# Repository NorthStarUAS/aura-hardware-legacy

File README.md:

# AuraUAS Autopilot Hardware

This is a repository of hardware designs that have evolved out of the
AuraUAS project.  These designs serve the AuraUAS ecosystem.

## Version 1.0 - 1.4 (May 2015 - August 2016)

Beaglebone Black + Custom Cape + APM2

This is the first functional autopilot board design I created myself.
I have built up at least 4 flying autopilots from this design.
However, it leverages the old APM2 (atmega2560-based) board as the
sensor head.  This results actually are quite good, but it leads to a
stack of 3 boards and a fairly inefficient layout.  Also the APM2 is a
very old design now, has some limitations, and is only available through
clone outlets.

## Version 1.5 (January 2017)

Beaglebone Black + Custom Cape + Teensy-3.2

Although not listed as v1.5 in the file names, this is the logical
successor to the APM2-based board.  The APM2 is dropped and replaced
by a more modern teensy-3.2 paired with an IMU/Pressure breakout
board.  The teensy offers much more CPU power, more memory, better
ADC's, and native 3.3v ttl logic levels.

The system was breadboarded and the overall concept proved out.
However, before this design was finished or built, the pocketbeagle
became available.  This has prompted me to move to the next iteration.

## Version 2.0 - 2.1 (January 2018)

Pocketbeagle + Teensy-3.2 + Custom Board (designed with Express PCB)

This is a single board that combines a pocketbeagle + teensy + imu
breakout + voltage regulator + connectors in a single board package
that has only slightly larger footprint compared to the original
beaglebone.

I ordered a test run of the v2.0 board and built up one to full flight
status.

This board was designed with the Express PCB software which also
requires ordering your boards from Express PCB.  The trade off is ease
of design versus flexibility and cost.

## Version 2.2 (February 2018)

Pocketbeagle + Teensy-3.2 + Custom Board (KiCad + Oshpark)

The next evolution of the board is a redesign in KiCad.  The main
benefit is the ability to order the design from a multitude of board
houses, and possibly even do a pick and place shop at some point in
the future.  This gives the most flexibility and less expensive board
runs.

Oshpark is a great inexpensive option.  They can suck in my KiCad pcb
file directly, and they are open-source and community-sharing
friendly.

Major updates:
- Switch to the awesome KiCad PCB design tool.
- Rearrange and move some parts to shrink the board footprint and
  simplify trace routing.
- Cleans up a few small goof ups in the v2.0 design.
- Switch to the TSR2-2450 power supply (functionally similar but
  slimmer and cleaner looking.)
- Add a voltage divider/sensor circuit for main input battery voltage
  (to complement the regulated voltage sensor.)
- Switch to a robust screw terminal connector for main power.

## Version 2.3 (March 2018)

Pocketbeagle + Teensy-3.2 + 2 Layer Custom Board (KiCad + Oshpark)

Major updates:
- Reverse TX/RX on GPS and Telemetry ports to match drone code
  standard (big dohhh!!! while assembling the first v2.2 board)
- Slide screw terminal slightly towards board edge to give more space
  to the resistors.
- Clearly mark pin 1 on TSR2-2450 connector to help avoid assembly
  mistakes.
- Relocate capacitor away from corner mounting hole.
- Draw bigger usb port outlines on teensy/pocketbeagle to match reality.
- Space sbus and atto connectors exactly 0.2" from ends of PWM block.-
  Experiment with KiCad's autorouting feature.
- Many small component placement and trace routing adjustments for better
  fit and aethsetics.

## Overview

These board designs support the AuraUAS autopilot flight code and
firmware.  The goal is to offer a relatively simple DIY "kit build"
solution for fixed wing UAV autopilots.  Attention is put towards
using inexpensive, but powerful off the shelf components.  Assembly is
relatively simple (mostly 0.1" header soldering.)  Overall cost is
comparable to other small UAV autopilot systems.

The basic architecture of the system employs a 'little' processor and
a 'big' processor working together as a distributed system.  The
little processor handles all the hard real time sensor I/O tasks.  The
big processor does all the heavy lifting, ekf, control, navigation,
logging, communication, and higher level logic and functions.

This system has been developed based on experience with UAS flight
control hardware, software, and flight test experience starting around
2005.  There is a fair bit of thought, experience, different ideas
tried, and lessons learned the hard way that have gone into the design
choices, development, and tuning of this system.

The following information needs to be reviewed and updated, but is
still mostly reliable.

## Primary design goals

- Maximize use of existing mature, inexpensive, and widely available
  sub-components.
- Minimize amount of custom electronic circuits, soldering, and cabling.
- Easy assembly/fabrication from kit (mostly 0.1" header soldering.)
- Minimize external wiring rats nest by pushing as many connections as
  possible onto the cape.
- High performance, high reliability, production quality flight
  results.

## Features

- Beaglebone/Linux based flight control system (big processor).
- Teensy/arduino based sensor interface (little processor.)
- SBUS RC Inputs (SBUS receiver required)
- 8 PWM Outputs (PWM servos required)
- MPU-9250 IMU, BMP[12]80 pressure sensor.
- 5v 2A power regulator on board.
- Attopilot (volt/amp) sensor interface for main battery.
- Avionics/main voltage sensing on board.
- Pocketbeagle console UART exposed.
- Supports industry standard (mRo) external devices: ublox 8 gps,
  900mhz radio modem, i2c based airspeed sensor.
- Mature firmware, autopilot flight code, and ground station interface.

## Power

- Input power can be anything that ranges from 6.5-36 volts.
- The board includes a 5V 2A regulator to provide clean stable power
  for all the avionics (pocketbeagle, teensy, gps, telemetry, RC
  receiver, etc.)
- Servos are powered from some external source arranged by the
  integrator (for example from the ESC via the throttle channel.)

## Communication

- Supports a variety of 5v (3.3v TTL) radio modems such as Freescale,
  mRo, and Digi Xtend.
- Exposes the mini-usb port on both the Teensy and the Pocketbeagle
  for updating firmware or debugging.
- Exposes the beaglebone UART0 (console) for additional communication
  and/or debugging the beaglebone.

## Cost

This board is not available for sale as an assembled unit.  However,
you are welcome to download the design and order it through Oshpark
(or any other board service.)  You can purchase all the components and
populate the board yourself with only minimal soldering skills.  I
estimate it will cost about $100/ea to assemble a full board.  Most
items can be purchased with free shipping.

The external components such as gps, radio modem, receiver, attopilot
volt/current sensor, etc. need to be purchased separately.  These are
things that are required for any autopilot system.

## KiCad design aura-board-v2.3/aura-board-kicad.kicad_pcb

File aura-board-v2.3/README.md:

# AuraUAS Autopilot Board

## Assembly Instructions and Check List

I recommend you print out these instructions on paper and actually
check off each step as it is completed.  Some steps cannot be
completed out of order!  If you work carefully and don't need to
resolve any major goof ups, I think most people can do this assembly in
2-3 evenings.

### Tools required

- [ ] A nice solder station such as a Weller WES51.  Right now I like
  600-650F for soldering 0.1" header pins.
- [ ] A volt meter and continuity checker.
- [ ] A small clipping pliers / wire cutter.
- [ ] Needle nose pliers.
- [ ] Lighted magnifying lens (if over 40.)
- [ ] 6.5 - 36V power supply.  I have a bench power supply from Extech
  that allows me to vary the voltage and shows me the current draw,
  but a battery or simple wall wart could work fine too.

### Install Power Subsystem

- [ ] Install 3.5mm screw terminal block.
- [ ] Install TSR2-2450 voltage regulator.  Note: pin 1 on the
  TSR2-2450 has a white dot next to it.  This corresponds with the
  hole nearest the edge of the board.
- [ ] You can go ahead and power up the board at this point (I
  recommend using < 20 volt supply until the capacitor is installed.)
  Using the schematic and board layout, test all the 5v points to make
  sure power is getting to the correct locations.
- [ ] Install the 22uf63v capacitor being careful to note polarity.
- [ ] Install the 3 x 1k ohm resistors. You might find a needle nose
  pliers helpful to gently pull on the wires from the back side and
  help the resister fully seat in place.
- [ ] Install the 10k ohm resistor.  Polarity does not matter with
  resistors.  Clip off the excess wire from the back of the board.
- [ ] Go ahead and power up the board again.  Test that pin-hole A0 on
  the teensy footprint reads about 1/11 of your input voltage.  Test
  that pin-hole A1 reads about 2.5 volts.

### Install the Teensy-3.2

- [ ] Carefully scratch between the two pads on the reverse side of
  the board to disable USB power to the teensy.  This is important
  because the teensy-3.2 is not tolerant of being powered by both usb
  and onboard power simultaneously.
  - If you forget this step before installing the teensy, there is no
    way to fix it!  But there is a work around ...
  - The recommendation is to rig up a standard USB cable with
    the red power line snipped and still safely upload firmware to your
    teensy while it is powered by the board regulator.
  - It is just annoying because you have to remember to use the
    correct usb cable or you may significantly shorten the life of your
    teensy.
  - I recommend you clearly mark the usb port on the teensy to remind
    yourself to always use your special non-power usb cable.
- [ ] Clip rows of 0.1" header pins to fill the available holes
  between the teensy and the AuraUAS board.
- [ ] Test fit the teensy, making sure you are not shifted up or down
  by one pin.  The teensy should be centered on the footprint outline
  drawn on the board.  The teensy usb port should be at the top edge
  of the board as shown in the footprint outline.
- [ ] Carefully solder all the pins from the top side.
- [ ] Last chance!  Make sure you scratched apart the two pads on the
  bottom of the teensy.
- [ ] Flip the board over and carefully solder all the pins from the
  bottom side.
- [ ] Use your wire cutter to carefully clip all the excess length of
  the back side pins off the board.
- [ ] Power up the board.  A stock teensy should blink it's LED light
  about once per second if it is getting power properly.
- [ ] Test that you are reading 3.3 volts at the MPU-9250 breakout
  board 3.3 pin hole.
- [ ] You can install the teensy-3.2 firmware (aura-sensors) now if
  you wish or wait until later.

### Install the CJMCU MPU-9250 breakout board

- [ ] Follow the same basic technique used for the teensy.
- [ ] Clip a continuous row of 5 x 0.1" header pins (The breakout
  board may come with pins.)
- [ ] Carefully position the board (supporting the side opposite of
  the pins with a spare header pin on it's side) and solder the pins
  from the top of the board. Note that it may be a tight fit depending
  on which board you get.
- [ ] Flip the board over and solder the back side pins.  *Important:*
  be careful to ensure the breakout board is as flush as possible and
  square with the AuraUAS board. Your IMU is on this board so it the
  more accurately you place this board, the better life will be when
  it comes time to fly.
- [ ] Don't forget to clip off the excess pin material on the back
  side of the board.
- [ ] Now you can power up the board and test the firmware is able to
  read the IMU!

### Install the Pocketbeagle

- [ ] Follow the same basic procedure as the teensy and the IMU
  breakout boards.
- [ ] Clip individual and pair-wise 0.1" pins to fill in the pin-holes
  that are used by the teensy.  8 x 2-pin pairs + 1 individual pin is needed.
- [ ] Carefully position the pocketbeagle on the board.  Before
  soldering, make sure the pocketbeagle is lined up with the footprint
  lines, the usb port is facing the top side of the board, and that
  there are no missing pins.  Now go ahead and solder the pins from
  the top side.
- [ ] Flip the board over and solder the pins from the backside.  Then
  clip off the excess pin length.
- [ ] Go ahead and power the board up again.  The pocketbeagle has a
  blue led that should light up.
- [ ] If you have an SD card prepared, you can insert it and fully
  boot up the pocketbeagle, connect to a laptop via the usb port, log
  in like it's any other beaglebone in the world, and you should be do
  all sorts of linux stuff.

### Install the RC Connectors

- [ ] Clip off 3 strings of 8 x 0.1" headers to complete the PWM
  output block.  Solder these on from the back.  A servo connector
  plugged into one or both ends can really help keep their alignment
  right on while you solder them in.
- [ ] Clip off 2 strings of 3 x 0.1" headers for the SBUS input
  connector and the Attopilot connector.  Solder these in.  I often try
  to block up the connector is it is positioned correctly.  Then I
  solder one pin and check for position and alignment.  If anything is
  off I can reheat that one pin and fix it.  Then once everything is
  double checked good and lined up and in the right place, I finish
  soldering the remainder of the pins.

### Install the Picoblade (or DF-13) connectors.

Integrator's choice of connectors here.  Sorry that JST-GH doesn't
have a through-hole variant so we are stuck with one of these other
connectors.  mRobotics should have JST-GH -> Picoblade and JSG-GH ->
DF-13 cables available, so pick your favorite and go with it.

These connectors have 1.25mm spacing so they are a bit trickier than
the 0.1" inch connectors.  Just be super careful, use a small bit of
solder, and remember heat and surface tension should make the solder
go where it needs to go and no further.  Be careful not to slather in
too much solder and bridge two adjacent pins!

Again, I recommend doing your best to block up and align the
connector, then solder just one pin.  Carefully check position and
alignment.  It's easy to reheat that one pin and make adjustments.
When you are happy, solder the remaining pins.

- [ ] Install the 6-position telemetry and gps connectors.  (Note the
  board can support soldering a 5-position connector.  You can review
  the schematic and board layout to figure out the proper position.)
- [ ] Install the 4-position i2c connector.  Again, mRobotics is your
  cable adapter friend.
- [ ] Optionally install the 6-position BBCON connector.  This gives
  you access to the Pocketbeagle console for debugging or possibly
  another uart for some future use.

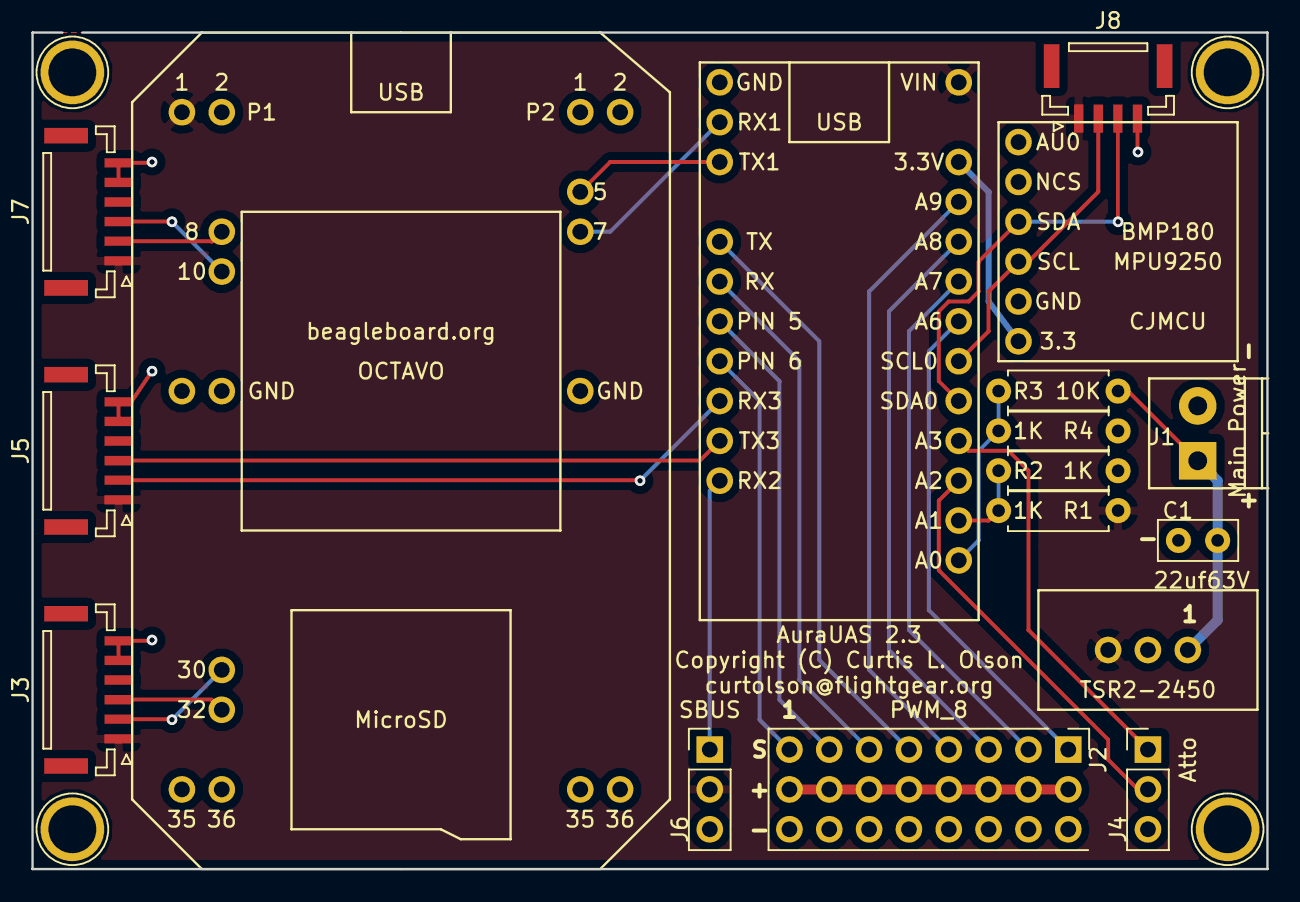
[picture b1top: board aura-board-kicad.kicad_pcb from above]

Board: 2 copper layers, 78.7 x 53.3 mm, 21 parts (0 on the bottom side), 27 nets.

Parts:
C1: 22uf63V; C_Disc_D5.0mm_W2.5mm_P2.50mm
J1: Main Power; TerminalBlock_Pheonix_PT-3.5mm_2pol
J2: PWM_8; PWM_3x08
J3: BBCON; JST_GH_BM06B-GHS-TBT_06x1.25mm_Straight
J4: Atto; Pin_Header_Straight_1x03_Pitch2.54mm
J5: GPS; JST_GH_BM06B-GHS-TBT_06x1.25mm_Straight
J6: SBUS; Pin_Header_Straight_1x03_Pitch2.54mm
J7: Tele; JST_GH_BM06B-GHS-TBT_06x1.25mm_Straight
J8: I2C0; JST_GH_BM04B-GHS-TBT_04x1.25mm_Straight
MH1, MH2, MH3, MH4: 1pin
R1, R2, R4: 1K; R_Axial_DIN0207_L6.3mm_D2.5mm_P7.62mm_Horizontal
R3: 10K; R_Axial_DIN0207_L6.3mm_D2.5mm_P7.62mm_Horizontal
U1: TSR2-2450
U2: PocketBeagle
U3: Teensy-3.2
U4: CJMCU

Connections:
+3V3: U3.31, U4.1
+5V: J3.1, J5.1, J6.2, J7.1, J8.1, R1.2, U1.3, U2.1, U3.33
/ATTO_AMPS: J4.2, U3.23
/ATTO_VOLTS: J4.1, U3.24
/AVIONICS_VCC: R1.1, R2.2, U3.22
/GPS_RX: J5.3, U3.10
/GPS_TX: J5.2, U3.9
/I2C0_SCL: J8.2, U3.26, U4.3
/I2C0_SDA: J8.3, U3.25, U4.4
/MAIN_VCC: R3.1, R4.2, U3.21
/MODEM_RX: J7.3, U2.10
/MODEM_TX: J7.2, U2.8
/PWM1: J2.1, U3.8
/PWM2: J2.2, U3.7
/PWM3: J2.3, U3.6
/PWM4: J2.4, U3.5
/PWM5: J2.5, U3.30
/PWM6: J2.6, U3.29
/PWM7: J2.7, U3.28
/PWM8: J2.8, U3.27
/SBUS_RX: J6.1, U3.11
/UART0_RX: J3.3, U2.32
/UART0_TX: J3.2, U2.30
/UART1_RX: U2.43, U3.2
/UART1_TX: U2.41, U3.3
GND: C1.2, J1.2, J2.10, J3.5, J3.6, J4.3, J5.5, J5.6, J6.3, J7.5, J7.6, J8.4, R2.1, R4.1, U1.2, U2.15, U2.16, U2.51, U3.1, U4.2
VDD: C1.1, J1.1, R3.2, U1.1

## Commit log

2015-06-02 Initial revisions committed to the repository.
2015-06-02 Added more info.
2015-06-03 Add a photo of the actual board prototype.
2015-06-03 Add a picture of the 1.0 layout.
2015-06-03 Update some wording.
2015-06-03 Add a first pass at license/copying terms ... to be refined and updated later (probably by choosing from an existing license that mostly covers my intensions.)
2015-06-03 Layout picture for version 1.1
2015-06-03 Oops, fix file extension.
2015-06-03 Update perimeter outline.
2015-06-03 Update license terms to creative commons attribution + share alike.
2015-06-04 After checking out DF13 connections now that cables arrived, I discovered that TX/RX were reversed on the APM2 connection. This is fixed in both the 1.0 and the 1.1 versions of the board.
    On the radio modem connector I had grounded both pins 5 and 6 to accept
    either a 5 or 6 position connector, but upon testing, if this is grounded
    on a 6 position cable, it puts the radio modem into bootloader mode, so
    I have removed the grounding connection on pin 5. A 5 position connector
    could still be used with a bit of extra work on the backside to ground pin 5.
2015-06-05 Shift apm mounting holes slightly aft to give a bit more clearance from the bb power barrel connector up front.
2015-06-08 Standardize on JST-PH-2 connector for main power into the board. This will then feed the ezsbc.com 7.2-40v in, 5v out / 1a out voltage regulator. Servos will be powered by the host aircraft's ESC (wi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
2015-06-08 Final changes before ordering 3 miniboards. (Including a JST-PH-2 power connector if I didn't mention that earlier.)
2015-06-09 Finalize 1.1 layout image.
2015-06-23 Shrink ground plane so it does not run all they way up to the board edge.
2015-12-09 Shrink ground plane so it doesn't extend to edge of board. Integrate Pololu D24V22F5 (5.0v 2.0 amp voltage regulator) Remove APM2-mini support (didn't like the hydra of cheap wires it included.)
2015-12-09 Not sure what changes are represented here, but I am jumping to v1.3 anyway and leaving the APM2 mini and ezsbc power supply behind.
2015-12-09 Trace tweaking.
2015-12-09 Make sure power supply is grounded to ground plane.
2016-08-10 New updates to board layout: - Remove specific cape-side apm2 power connector in favor of a simpler 5v "rc" style connector - Move 5v external bus where apm2 power connector is now - Prefer pololu 5v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
2016-08-10 - Add room for second (optional) 5V/5A power regulator for powering the servo bus. This would enable operation of servos independent of the main motor and main motor BEC. - Do a fair bit of rearrangi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
2016-08-10 Nearly final adjustments for v1.3 layout? :-)
2016-08-10 Freshen the readme to reflect latest design changes.
2016-08-10 Photo of v1.1 assembled.
2016-08-10 Fix a typo.
2016-08-10 Ordered v1.3 boards (x3) so now it's time to start the v1.4 development off with a few cosmetic labeling changes.
2016-08-10 More updates to the README
2016-08-10 A bit more word smithing.
2016-08-10 A few more edits ... I need to stop looking at the README and go do something else now. :-)
2017-08-03 Roughing in a schematic for a new cape. This one would drop the legacy APM2 board and replace it with a Teensy-3.2 and MPU-9250 breakout board. The net result should be cleaner with far better perfor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
2017-08-03 Clean up a few connection routes.
2017-08-03 Added an 'abbreviated' beaglebone P9 header to schematic.
2017-08-03 Updated the readme a bit. I will need to make more changes in the future as the teensy-based design solidifies.
2017-08-04 Added voltage divider resistors for measuring avionics and main voltages.
2017-08-06 Add external I2C connector and GPS-UART connector.
2017-08-06 Various cleanups and tweaks and rearrangements.
2017-08-07 A few more tweaks in the process of forever tweaking.
2017-08-07 Add attopilot connector (to two analog inputs.)
2017-10-29 Switch to MIT license.
2018-01-11 ExpressPCB custom component library.
2018-01-11 Distinguish version.
2018-01-11 Initial revision.
2018-01-11 Initial revision of a pocketbeagle/teensy single board AP.
2018-01-11 Simplified pocketbeagle schematic part for AuraUAS design.
2018-01-11 Touch the readme a bit.
2018-01-11 Fix the pololu regulator component Add stripped down versions of teensy and pocketbeagle components.
2018-01-11 Just a rough start on a new board layout.
2018-01-11 Much tidying up is still needed, but most of the basic components and connections are now in place.
2018-01-12 Clean up some routing, connect IMU via I2C to Teensy.
2018-01-12 Rename ...
2018-01-13 Totally flipped the orientation of everything.
2018-01-13 Added external i2c connector (4x1 0.1" header). Currently not powered because I don't know if it should be 5v or 3.3v power to an external device?
    Flipped the SBUS and ATTO external connectors to align ground/signal with
    other connectors.
2018-01-13 Simplify Teensy->J7 traces.
2018-01-13 Moved the SBUS header in order to simplify traces a bit more.
2018-01-18 Added voltage divider circuits for sending main input voltage and avionics voltage.
2018-01-18 Add some connector labels, fiddle with a couple traces ... getting close to ready to order.
2018-01-19 Sync with latest save.
2018-01-20 Switch to I2C pressure sensor and drop the idea of using the old 5v analog MPXV7002DP differential pressure sensors. The teensy doesn't support 5v analog range, only 3.3v. Mrobotics and BFS both make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
2018-02-01 Starting v2.1: - Somehow after moving the teensy, I never got the ground pin connected to the back plane, now fixed. - Picked too small holes for the MPU-9250 breakout, now fixed. - More updates to c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
2018-02-01 reorg.
2018-02-02 Begin some mods based on experience with first board run.
    - Shift everthing up to the "top" edge of the board for less wasted space.
    We are going to try to shrink the layout in both dimensions.
    - Other planned changes:
    o Switch to a screw terminal block for main power in.
    o Drop the pololu voltage regulator and Switch to a TSR 2-2450 voltage
    regulator (with 22uf 63v capactor.) This should yield a smaller foot
2018-02-05 Begin dabbling with a kicad schematic for the next auraboard version.
2018-02-05 Updates.
2018-02-05 Add attopilot connector.
2018-02-06 Add screw terminal for external power hookup.
2018-02-06 Added voltage divider circuits for sensing avionics and main voltages.
2018-02-06 Add capacitor to input power circuit.
2018-02-06 Add one missing (VIN) connection.
2018-02-06 Aligning and spacing on the schematic.
2018-02-06 Attempt to draw power busses correctly in schematic.
2018-02-06 Annotate schematic.
2018-02-06 Passed the electrical rules check on the first try so now we can generate the netlist file.
2018-02-06 Nudge white space on the schematic, generate a pdf version.
2018-02-06 Freshen the README.
2018-02-06 Working my way through the process of drawing custom footprints for the layout.
2018-02-06 Begin pcb layout arrangment of components.
2018-02-06 Fix a wrong units issue.
2018-02-07 Start adding a few easy traces.
2018-02-07 Shuffle PWM assignment on teensy (schematic) to make tracerouting more convenient. Work on trace routing. (Still need to set up a ground plane and create the power bus.)
2018-02-07 Update the pdf version of the schematic, add a png/bitmap version.
2018-02-07 Add a ground plane.
2018-02-07 More trace routing and tweaking.
2018-02-07 More trace routing. Position resistors for voltage divider/sending circuits. Add mounting holes (3mm).
2018-02-07 Add a +5V power bus plane on the top layer.
2018-02-07 Add pin headers to complete pwm header block.
2018-02-07 Add a proper 3x08 PWM block with ground pins and the power bus tied together but not connected to board power.
2018-02-07 Swich to picoblade 1.25mm external connectors. DF-13 will also fit here. Pins 5 and 6 both tie to ground. This means the assembler can pick 5 or 6 pos headers depending on their needs. This offers so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
2018-02-07 Increase pad diameter (inner and outer) on all my project footprints to match standard 0.1" pin dimensions.
2018-02-08 Clean up a small mess after trying to change pad size on all my custom footprints.
2018-02-08 Move some of the F.Fab labels to F.SilkS so they show up on the final board.
2018-02-08 Make picoblade 6-pos aux-ground pin trace connection slightly thicker.
2018-02-08 Add my name and board version to the silkscreen.
2018-02-08 Slightly painful, but I moved the teensy 0.05" away from the pocketbeagle to make sure they aren't so close together there is a chance they would conflict. This led to quite a bit of cascading work w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
2018-02-08 labelling tweaks.
2018-02-08 Label adjustments.
2018-02-08 Switch to a larger (3.5mm) screw terminal block for main power.
2018-02-08 Project file / directory structure renaming for better clarity.
2018-02-08 More renaming of directory layout.
2018-02-08 Small labelling tweak.
2018-02-08 A few small tweaks with labeling. Nudge one connector and a couple traces.
2018-02-09 Endless tiny tweaks and adjustments continue ...
2018-02-10 Follow the standard drone-code pin order for external connectors. Fiddle with a couple traces to hopefully shorten and simplify.
2018-02-18 Update schematic plot after noticing it was a bit out of date.
2018-02-18 Freshen the README
2018-02-18 Fix some typos.
2018-02-28 Write up some basic assembly instructions as I go through the first board assembly.
2018-03-01 More updates.
2018-03-02 Starting point for v2.3 improvements.
2018-03-03 Add a picture to the readme.
2018-03-10 Initial v2.3 design fixes and tweaks: - reverse tx/rx on gps and telemetry (big dohhh!) - slide screw terminal slightly towards board edge - mark pin #1 on TSR2-2450 connector clearly - relocate capa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
2018-03-10 Bump up the version number in the board label Fiddle with traces a bit more.
2018-03-10 Spell check.
2018-03-10 Copy over latest readme changes from v2.2 as the starting point for v2.3
2018-03-10 Add an Errata section.
2018-03-10 Updated wording.
2018-03-10 More word tweaks.
2018-03-10 Various small positional adjustments to give better clearance for the upper right mounting hole. Various trace route tweaks for aesthetics.
2018-03-10 Updated info for v2.3
2018-03-10 Add a picture of the front of the raw board before components attached.
2018-03-11 Add pdf plot of schematic.
2018-03-13 Switch to JST-GH surface mount connectors.

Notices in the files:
aura-board-v2.3/aura-board-kicad.kicad_pcb:
Copyright (C) Curtis L. Olson
